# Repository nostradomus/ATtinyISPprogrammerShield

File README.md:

# ATtiny ISP programmer shield for Arduino UNO boards

## What

This repo provides you with all necessary info (and files) to build an Arduino shield to program Atmel's **attiny** 𝜇-controllers. For that matter, the underlying Arduino board should be loaded with the ISP-programmer sketch (built-in example).

## Why

Often, one of these "tiny" chips is largely powerful enough for the design of small projects. During the design phase, I however got tired of wiring up things on a breadboard. As (like many people) I was having a spare UNO, which could serve as an ISP programmer, I decided to design a minimalistic shield to fit on top of it.  

## How

The shield has been designed with EAGLE from AutoDesk/CadSoft. This shield [project](eagle-files/) can be opened with the free version [(download here)](http://www.autodesk.com/products/eagle/free-download). In order to keep things simple, the V1 PCB can be etched single-sided, as the top-layer only contains a couple of short connections (which can easily be replaced by wire-bridges). The V2 PCB (a real double-sided version) has optimised routing and ground-pours. Only [through-hole components](BOM.md) have been used in order to make the built also feasible for any beginner. In the [pdf-folder](pdf-files/) of this repo pdf versions of all important EAGLE views are available, for those not wanting to install EAGLE. Pay attention to print the bottom and top-layer layouts **without re-sizing** (1:1). To have the printed circuit board built by a commercial PCB-shop, the [gerber-files](gerber-files/) are also available.

Currently, unpopulated V2 boards are still available from our workshop. If interested, [contact us via   :email:](http://nostradomus.ddns.net/contactform.html).

## Technical details

### What’s on the board

The board is fit with 3 IC sockets (8, 14 and 20 pin), for the 3 types attiny’s. **Only one chip should be fit at a time** :exclamation: On the prototype, pin headers with double functionality have been mounted. Pins on the bottom-side to fit on the Arduino board, and feed-through female headers on the top for easy access of all Arduino connections.
The push button, is connected to the reset lines of the attiny’s with a 10kΩ pull-up resistor. When the shield is cut correctly, the reset button for the Arduino UNO itself should still be accessible. In order to make the Arduino Uno work as an ISP programmer a 10µF capacitor needs to be connected on its reset-line.
Three LED’s are available to visualise the correct functionality of the programming procedure.
An optional AVR ISP socket has been foreseen in order to use the shield as stand-alone with a commercial programmer.

#### BOM - bill of materials

Part | Value | Package | Description  
---- | ----- | ------- | -----------                            
R1     | 10kΩ           | 0207/7         | resistor                                            
R2,3,4 | 270Ω           | 0207/7         | resistor                                            
C1     | 10µF/16V       | E2,5-6E        | polarized capacitor                                 
C2,3,4 | 100nF          | C050-025X075   | capacitor                                           
LED1   | 3mm yellow     | 3mm            | LED                              
LED2   | 3mm red        | 3mm            | LED                              
LED3   | 3mm green      | 3mm            | LED                                                                                             
IC1    | 8-pin          | DIL08          | IC socket                                                            
IC2    | 14-pin         | DIL14          | IC socket                                                                     
IC3    | 20-pin         | DIL20          | IC socket                                                                     
ICSP1  | 2x3 pin-header | 2x3            | AVR ISP-6 Serial Programming Header (optional)                                 
S1     | momentary      | 6x6x6mm        | momentary tact push button
S2	    | SPDT	          | MINI SWITCH 90 | mini toggle switch
CON1   | 6-pin          | SIL06          | long needle female stackable pin header strip
CON2,3 | 8-pin          | SIL08          | long needle female stackable pin header strip
CON4   | 10-pin         | SIL10          | long needle female stackable pin header strip

### How things work

First the the [ISP-programmer sketch](sketches/ArduinoISP.ino) (built-in example) should be loaded to the Arduino UNO board. During that operation, switch S2 should be set to 'PROG' (or remove the blue jumper JP1 on a V1 board). Select “Arduino Uno” as target board in the tools-menu. Load the ISP-programmer sketch with the “UPLOAD” button. Once loaded, the jumper can be put back to send your a sketch to your attiny 𝜇-controller.

To load a sketch to your attiny chip, make sure that the correct target board is selected in the tools-menu (you might need to download a specific library -> tools-menu, board manager). This time, use the “UPLOAD USING PROGRAMMER” option from the sketch-menu.

The 3 LED’s will tell you how things are going :
 - Green  : ISP programmer running
 - Yellow : uploading sketch
 - Red    : error  

### Proof of concept

So far, I have tested the shield with the below list of 𝜇-controllers :
 - attiny84
 - attiny85
 - attiny2313
 - attiny4313

 Any pin-compatible 𝜇-controller should work as well :
 - 8-pin  : attiny10/11/12/13/15/22/25/45/85
 - 14-pin : attiny24/44/84
 - 20-pin : attiny2313/4313
 (on condition of using the correct settings in your Arduino programming environment)

## Contributors

If you are having any good suggestions, just drop me a line [:email:](http://nostradomus.ddns.net/contactform.html).
If feasible, I'll be happy to implement any proposed improvements.
And if you are having lots of time, I'll be happy to share the work with you ;-).

## :globe_with_meridians: License

At this moment, there is no specific license attached to this project.

So, today, if you like it, have fun with it (at your own risk of course :-D), and especially, be creative.

Oh, and when using anything from this repository, it is highly appreciated if you mention its origin.

If you would like to use any of this work (or the whole project) for commercial use, first [contact us :email:](http://nostradomus.ddns.net/contactform.html), so we can add the appropriate license, which best fits your business.

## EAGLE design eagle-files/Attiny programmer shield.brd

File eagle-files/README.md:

This folder contains all files required to open the project in the EAGLE PCB software [(download here)](http://www.autodesk.com/products/eagle/free-download) : 

 - .epf : the project file as main entry point (is connected with the description file)
 - .sch : schematic file
 - .brd : pcb layout file
 
 These files should (grouped in a folder) either be copied in Eagle's project directory (see below image of the settings window). The Eagle directory settings also accept multiple paths. The Eagle syntax requires columns as path separators.

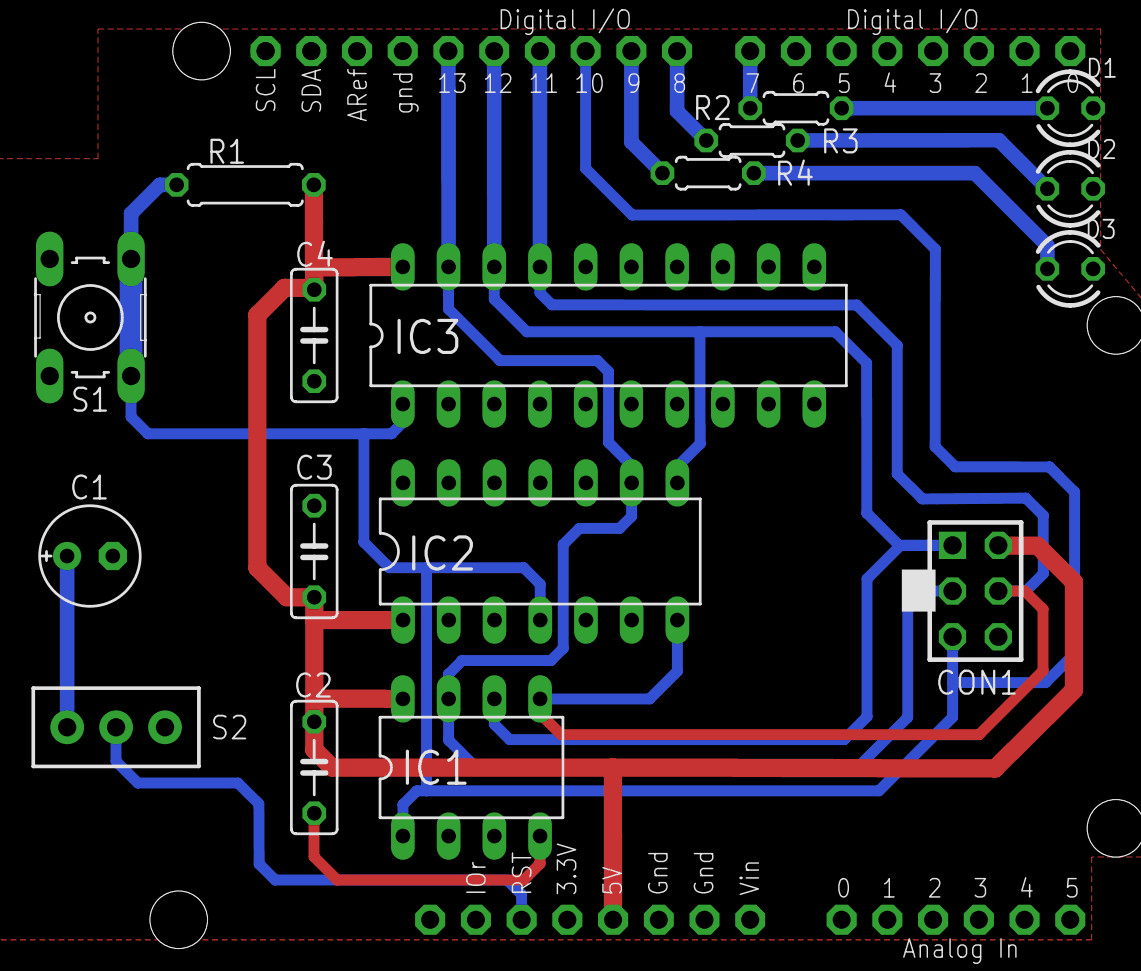
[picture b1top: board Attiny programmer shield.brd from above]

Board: 2 copper layers, 23 parts (0 on the bottom side), 14 nets.

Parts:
C1: 10µF/16V; E2,5-6E
C2, C3, C4: 100nF; C050-025X075
CON1: ICSP; AVR-ISP-6
D1: Yellow - programming; LED3MM
D2: Red - error; LED3MM
D3: Green - ISP running; LED3MM
IC1: attiny10/11/12/13/15/22/25/45/85; DIL08
IC2: attiny24/44/84; DIL14
IC3: attiny2313/4313; DIL20
R1: 10k; 0207/7
R2, R3, R4: 270; 0204/5
S1: Reset; B3F-10XX
S2: prog-mode; MINI_SPDT_SWITCH-9.0X4.0MM
U$1: Arduino Uno; ARDUINO-R3
U$2: COPYRIGHT-LOGO-3-B
U$3: 3X-LOGO-10-B
U$4: COPYRIGHT-LOGO-3-T
U$5: 3X-LOGO-5-B
U$6: 3X-LOGO-5-T

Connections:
+UB: C2.2, C3.2, C4.2, CON1.2, IC1.8, IC2.1, IC3.20, R1.2, U$1.5V
GND: C1.-, C2.1, C3.1, C4.1, CON1.6, D1.K, D2.K, D3.K, IC1.4, IC2.14, IC3.10, S1.3, S1.4, U$1.GND, U$1.GND1, U$1.GND2
MISO: CON1.1, IC1.6, IC2.8, IC3.18, U$1.D12
MOSI: CON1.4, IC1.5, IC2.7, IC3.17, U$1.D11
unnamed: C1.+, S2.3
unnamed: R4.1, U$1.D9
unnamed: R2.1, U$1.D7
unnamed: R3.1, U$1.D8
unnamed: D1.A, R2.2
unnamed: D2.A, R3.2
unnamed: D3.A, R4.2
unnamed: S2.2, U$1.RESET
RESET: CON1.5, IC1.1, IC2.4, IC3.1, R1.1, S1.1, S1.2, U$1.D10
SCK: CON1.3, IC1.7, IC2.9, IC3.19, U$1.D13

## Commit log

2020-07-02 BOM updated
